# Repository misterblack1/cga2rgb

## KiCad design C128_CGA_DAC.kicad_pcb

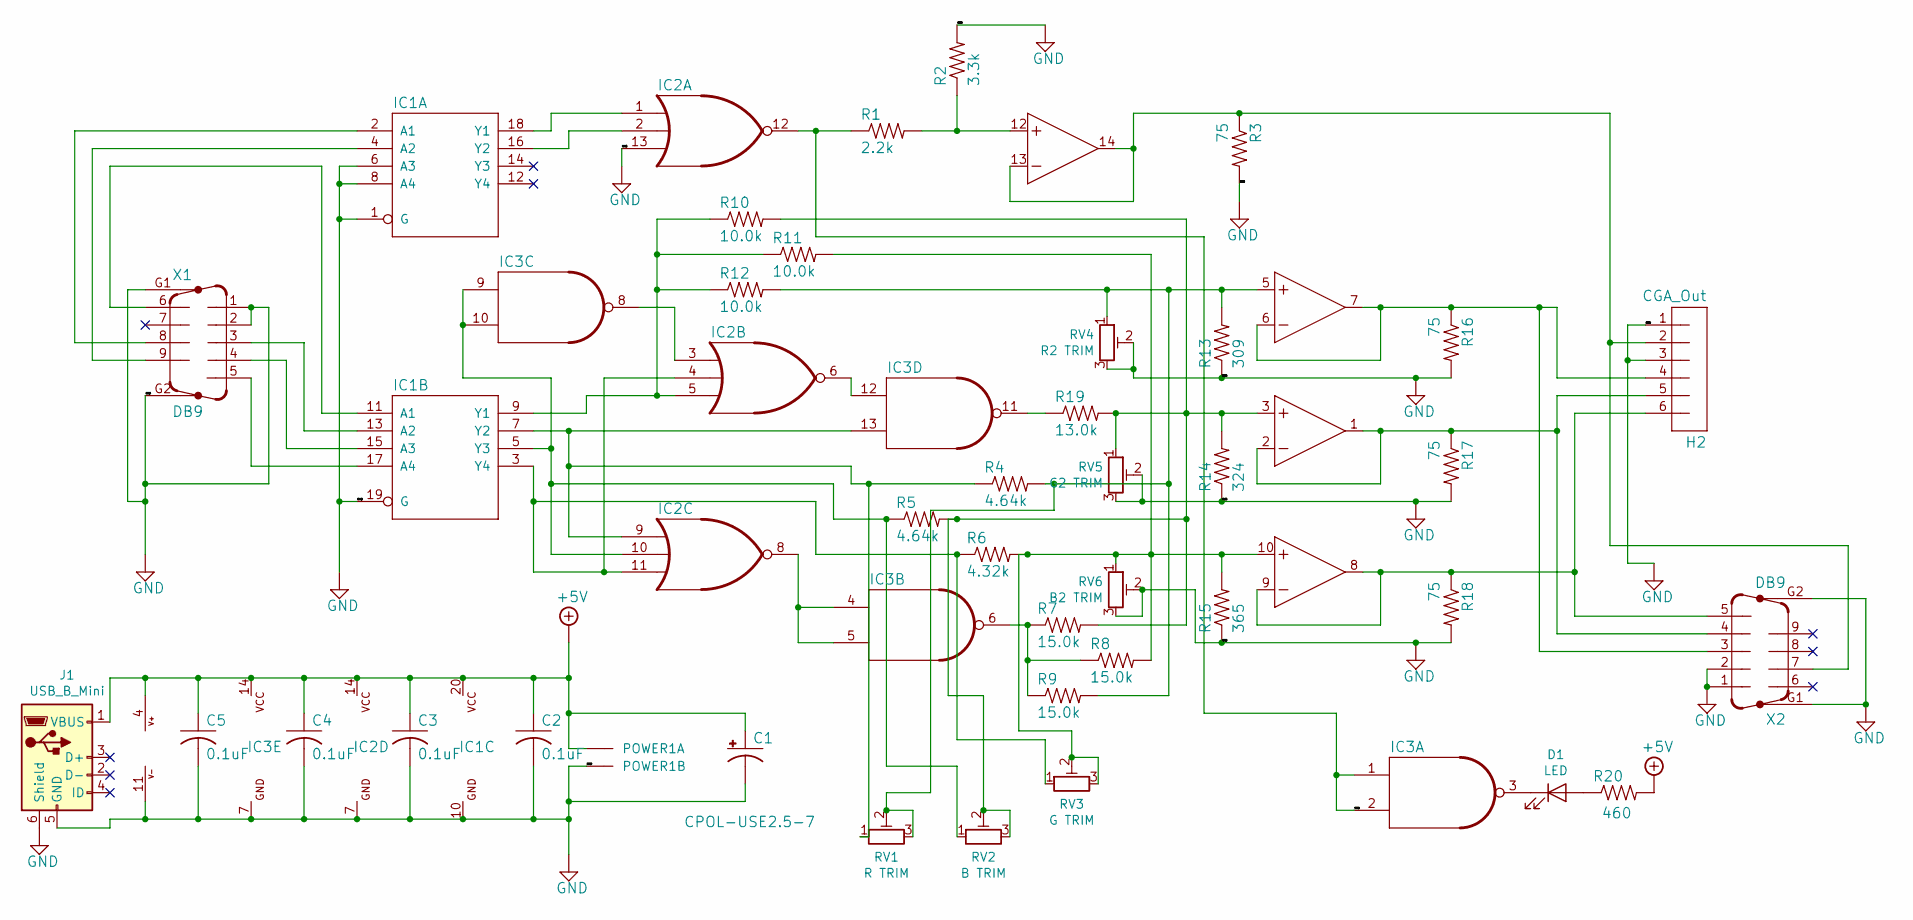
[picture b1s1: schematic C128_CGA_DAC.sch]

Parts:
C1: CPOL-USE2.5-7; E2,5-7
C2, C3, C4, C5: 0.1uF; C050-024X044
D1: LED; LED_D3.0mm
H2: CGA_Out; MA06-1
IC1: 74ACT244; DIL20
IC2: 74F27; DIL14
IC3: 74ACT00; DIL14
IC4: AD8044; DIL14
J1: USB_B_Mini; USB_Mini-B_Lumberg_2486_01_Horizontal
POWER1: 22-23-2021
R1: 2.2k; 0204_7
R2: 3.3k; 0204_7
R3, R16, R17, R18: 75; 0204_7
R4, R5: 4.64k; 0204_7
R6: 4.32k; 0204_7
R7, R8, R9: 15.0k; 0204_7
R10, R11, R12: 10.0k; 0204_7
R13: 309; 0204_7
R14: 324; 0204_7
R15: 365; 0204_7
R19: 13.0k; 0204_7
R20: 460; 0204_7
RV1: R TRIM; Potentiometer_Bourns_3296W_Vertical
RV2: B TRIM; Potentiometer_Bourns_3296W_Vertical
RV3: G TRIM; Potentiometer_Bourns_3296W_Vertical
RV4: R2 TRIM; Potentiometer_Bourns_3296W_Vertical
RV5: G2 TRIM; Potentiometer_Bourns_3296W_Vertical
RV6: B2 TRIM; Potentiometer_Bourns_3296W_Vertical
X1, X2: DB9; M09HP

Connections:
+5V: C1.+, C2.1, C3.1, C4.1, C5.1, IC1.20 (VCC), IC2.14 (VCC), IC3.14 (VCC), IC4.4 (V+), J1.1 (VBUS), POWER1.1, R20.2; also elsewhere on the board
GND: C1.-, C2.2, C3.2, C4.2, C5.2, H2.1, H2.3, IC1.1 (G), IC1.6 (A3), IC1.8 (A4), IC1.10 (GND), IC1.19 (G), IC2.7 (GND), IC2.12 (O), IC2.13 (I2), IC3.1 (I0), IC3.2 (I1), IC3.7 (GND), IC4.11 (V-), J1.5 (GND), J1.6 (Shield), POWER1.2, R1.1, R2.2, R3.2, R13.1, R14.1, R15.1, R16.2, R17.2, R18.2, RV4.2, RV4.3, RV5.2, RV5.3, RV6.2, RV6.3, X1.1, X1.2, X1.G1, X1.G2, X2.1, X2.2, X2.G1, X2.G2; also elsewhere on the board
unnamed: D1.1 (K), IC3.3 (O)
unnamed: D1.2 (A), R20.1
unnamed: H2.2, IC4.13 (-IN), IC4.14 (OUT), R3.1, X2.7
unnamed: H2.4, IC4.6 (-IN), IC4.7 (OUT), R16.1, X2.3
unnamed: H2.5, IC4.1 (OUT), IC4.2 (-IN), R17.1, X2.4
unnamed: H2.6, IC4.8 (OUT), IC4.9 (-IN), R18.1, X2.5
unnamed: IC1.2 (A1), X1.8
unnamed: IC1.3 (Y4), IC2.4 (I1), IC2.11 (I2), R6.1, RV3.1
unnamed: IC1.4 (A2), X1.9
unnamed: IC1.5 (Y3), IC2.10 (I1), IC3.9 (I0), IC3.10 (I1), R5.1, RV2.1
unnamed: IC1.7 (Y2), IC2.9 (I0), IC3.13 (I1), R4.1, RV1.1
unnamed: IC1.9 (Y1), IC2.5 (I2), R10.1, R11.1, R12.1
unnamed: IC1.11 (A1), X1.6
unnamed: IC1.13 (A2), X1.3
unnamed: IC1.15 (A3), X1.4
unnamed: IC1.16 (Y2), IC2.2 (I1)
unnamed: IC1.17 (A4), X1.5
unnamed: IC1.18 (Y1), IC2.1 (I0)
unnamed: IC2.3 (I0), IC3.8 (O)
unnamed: IC2.6 (O), IC3.12 (I0)
unnamed: IC2.8 (O), IC3.4 (I0), IC3.5 (I1)
unnamed: IC3.6 (O), R7.1, R8.1, R9.1
unnamed: IC3.11 (O), R19.1
unnamed: IC4.3 (+IN), R5.2, R7.2, R10.2, R14.2, R19.2, RV2.2, RV2.3, RV5.1
unnamed: IC4.5 (+IN), R4.2, R9.2, R12.2, R13.2, RV1.2, RV1.3, RV4.1
unnamed: IC4.10 (+IN), R6.2, R8.2, R11.2, R15.2, RV3.2, RV3.3, RV6.1
unnamed: IC4.12 (+IN), R1.2, R2.1

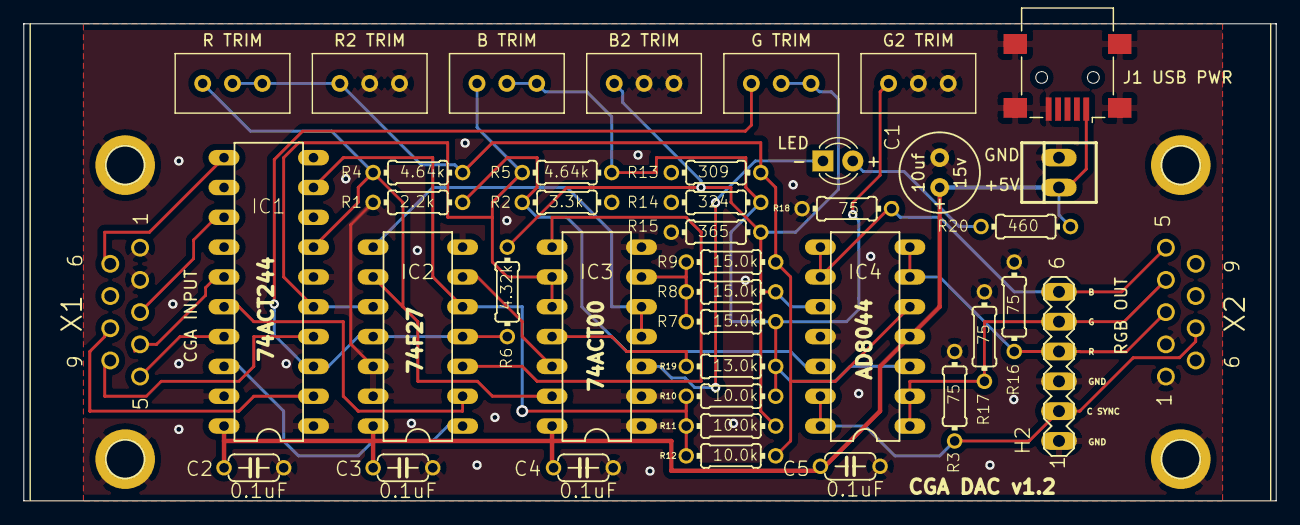
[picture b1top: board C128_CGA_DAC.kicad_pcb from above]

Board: 2 copper layers, 106.7 x 40.6 mm, 41 parts (0 on the bottom side), 29 nets.

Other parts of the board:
J1 USB PWR: USB_B_Mini; USB_Mini-B_Lumberg_2486_01_Horizontal

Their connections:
+5V: J1 USB PWR.1; also elsewhere on the board
GND: J1 USB PWR.5, J1 USB PWR.6; also elsewhere on the board
